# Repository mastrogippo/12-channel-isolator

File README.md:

## 12 channel isolator 

[Writeup and pics here](http://www.mastrogippo.it/2019/08/first-prototype-and-test-hardware/)

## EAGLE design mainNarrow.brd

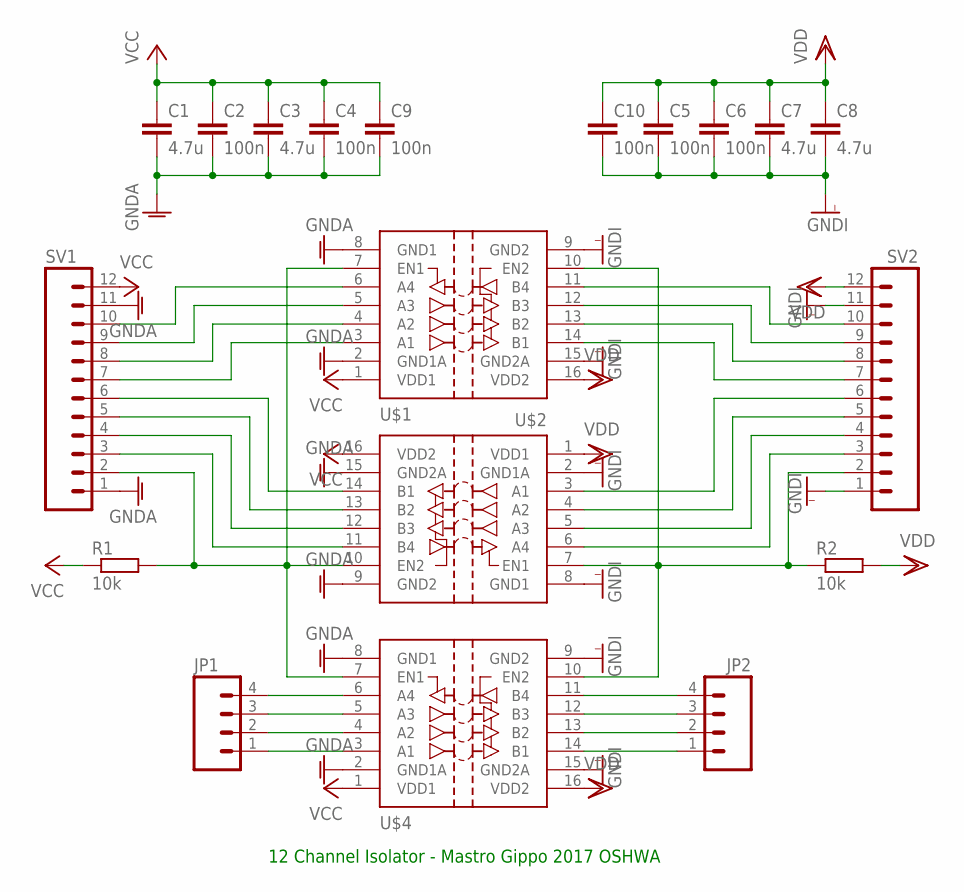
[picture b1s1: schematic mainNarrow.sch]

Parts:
C1, C3, C7, C8: 4.7u; C0805K
C2, C4, C5, C6, C9, C10: 100n; C0805K
JP1, JP2: M04LONGPADS; 1X04_LONGPADS
R1, R2: 10k; M0805
SV1, SV2: M12LONGPADS; 1X12_LONGPADS
U$1, U$2, U$4: SI8441IS1; SO16

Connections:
GNDA: C1.2, C2.2, C3.2, C4.2, C9.2, SV1.1, SV1.11, U$1.2 (GND1A), U$1.8 (GND1), U$2.9 (GND2), U$2.15 (GND2A), U$4.2 (GND1A), U$4.8 (GND1)
GNDI: C5.2, C6.2, C7.2, C8.2, C10.2, SV2.1, SV2.11, U$1.9 (GND2), U$1.15 (GND2A), U$2.2 (GND1A), U$2.8 (GND1), U$4.9 (GND2), U$4.15 (GND2A)
unnamed: SV1.10, U$1.6 (A4)
unnamed: SV1.9, U$1.5 (A3)
unnamed: SV1.8, U$1.4 (A2)
unnamed: SV1.7, U$1.3 (A1)
unnamed: R1.2, SV1.2, U$1.7 (EN1), U$2.10 (EN2), U$4.7 (EN1)
unnamed: R2.1, SV2.2, U$1.10 (EN2), U$2.7 (EN1), U$4.10 (EN2)
unnamed: SV1.6, U$2.14 (B1)
unnamed: SV1.5, U$2.13 (B2)
unnamed: SV1.4, U$2.12 (B3)
unnamed: SV1.3, U$2.11 (B4)
unnamed: SV2.9, U$1.12 (B3)
unnamed: SV2.8, U$1.13 (B2)
unnamed: SV2.10, U$1.11 (B4)
unnamed: SV2.7, U$1.14 (B1)
unnamed: SV2.6, U$2.3 (A1)
unnamed: SV2.5, U$2.4 (A2)
unnamed: SV2.4, U$2.5 (A3)
unnamed: SV2.3, U$2.6 (A4)
unnamed: JP1.1, U$4.3 (A1)
unnamed: JP1.2, U$4.4 (A2)
unnamed: JP1.3, U$4.5 (A3)
unnamed: JP1.4, U$4.6 (A4)
unnamed: JP2.1, U$4.14 (B1)
unnamed: JP2.2, U$4.13 (B2)
unnamed: JP2.3, U$4.12 (B3)
unnamed: JP2.4, U$4.11 (B4)
VCC: C1.1, C2.1, C3.1, C4.1, C9.1, R1.1, SV1.12, U$1.1 (VDD1), U$2.16 (VDD2), U$4.1 (VDD1)
VDD: C5.1, C6.1, C7.1, C8.1, C10.1, R2.2, SV2.12, U$1.16 (VDD2), U$2.1 (VDD1), U$4.16 (VDD2)

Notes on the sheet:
12 Channel Isolator - Mastro Gippo 2017 OSHWA

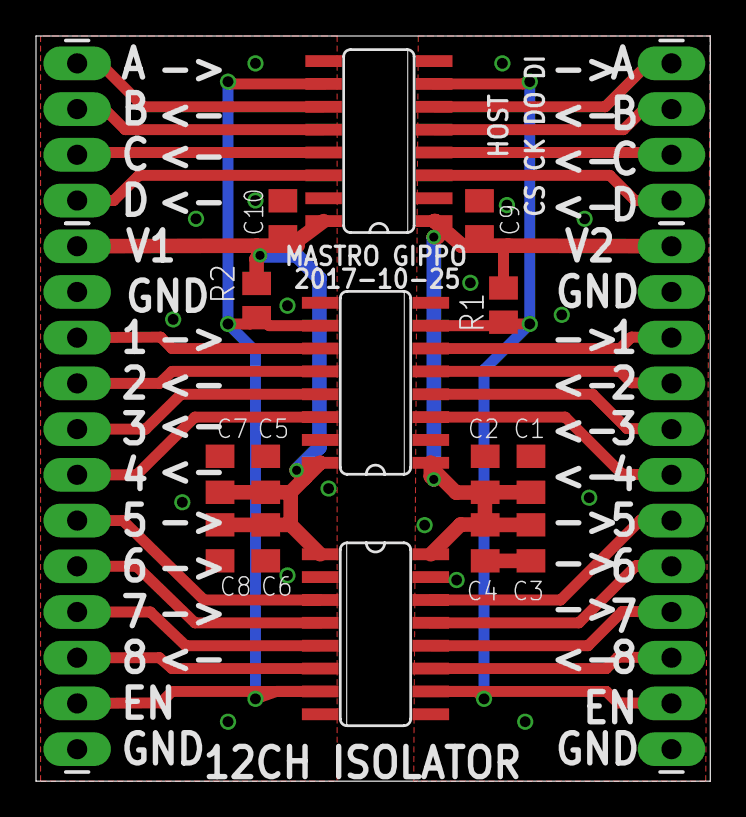
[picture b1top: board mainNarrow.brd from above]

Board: 2 copper layers, 37.5 x 41.4 mm, 20 parts (1 on the bottom side), 30 nets.

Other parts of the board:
U$3: OSHWLOGO_TOL_0.2

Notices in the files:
parts and their libraries:
SparkFun-Connectors: Licensing: Creative Commons ShareAlike 4.0 International - https://creativecommons.org/licenses/by-sa/4.0
